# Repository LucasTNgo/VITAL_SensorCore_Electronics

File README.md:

#VITAL Sensor Core Electronics

This ReadMe is empty for now.

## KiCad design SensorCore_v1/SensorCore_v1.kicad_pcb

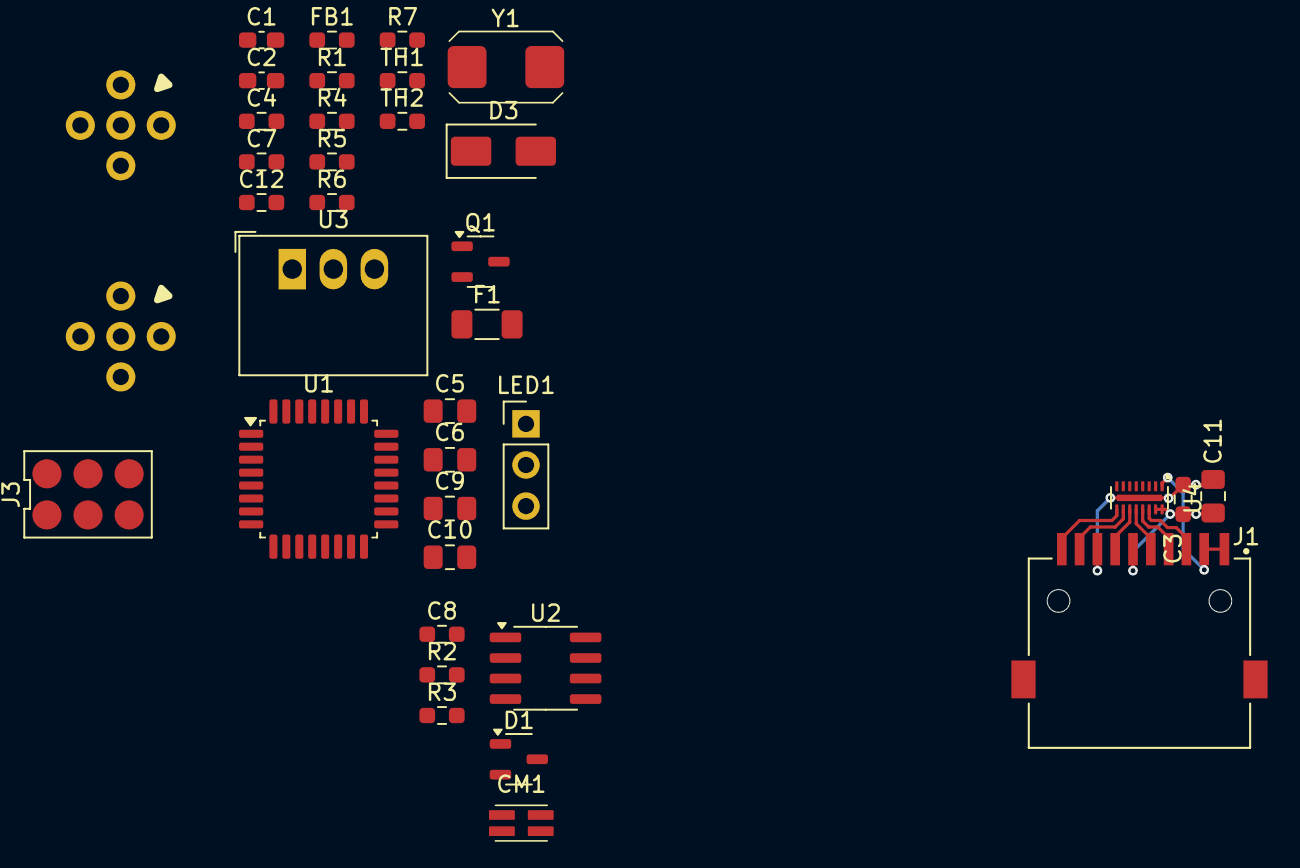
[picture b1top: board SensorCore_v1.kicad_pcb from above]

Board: 4 copper layers, 37 parts (0 on the bottom side), 33 nets.

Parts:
C1, C2: 27pF; C_0603_1608Metric_Pad1.08x0.95mm_HandSolder
C3, C4, C7, C8, C12: 100nF; R_0603_1608Metric_Pad0.98x0.95mm_HandSolder
C5, C6, C9, C10, C11: 10uF 16V; C_0805_2012Metric_Pad1.18x1.45mm_HandSolder
CM1: CM_Choke; CMChoke_2.6x1.2mm_HandSolder
D1: 12V TVS 2CH; SOT-23-3
D3: 12V TVS 1CH; D_SMA
F1: 100mA Polyfuse; R_1206_3216Metric_Pad1.30x1.75mm_HandSolder
FB1: FerriteBead; R_0603_1608Metric_Pad0.98x0.95mm_HandSolder
J1: Micro_SD_Card_Det1; CUI_MSD-11-A
J2, J4: M12x5 A-Type; M12x5_A_Circular_Connector
J3: 2x3 Header; 2x03_2.54mm_DIP_pogo
LED1: RG LED; PinHeader_1x03_P2.54mm_Vertical
Q1: DMN2310U; SOT-23-3
R1, R4: 100k; R_0603_1608Metric_Pad0.98x0.95mm_HandSolder
R2, R3: 10R; R_0603_1608Metric_Pad0.98x0.95mm_HandSolder
R5, R6: 1k; R_0603_1608Metric_Pad0.98x0.95mm_HandSolder
R7: 47k; R_0603_1608Metric_Pad0.98x0.95mm_HandSolder
TH1, TH2: NTC100k B3950 SMT; R_0603_1608Metric_Pad0.98x0.95mm_HandSolder
U1: STM32C092KCT6; LQFP-32_7x7mm_P0.8mm
U2: ATA6563; SOIC-8_3.9x4.9mm_P1.27mm
U3: R-78K3.3-1.0; Converter_DCDC_RECOM_R-78B-2.0_THT
U4: EMIF06-MSD02N16; OnSemi_UDFN-16-1EP_1.35x3.3mm_P0.4mm_EP0.4x2.8mm
Y1: 8MHz 16pF Load; Crystal_6x3.5mm

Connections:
+3V3: C3.2, C4.2, C5.1, C6.1, C7.2, C9.1, C11.1, J1.4 (VDD), J3.5, R7.1, TH1.1, TH2.1, U1.4 (VDD/VDDA), U2.5 (VIO), U3.3 (OUT), U4.15 (VCC), U4.16 (RDATA_VCC)
+5V: C8.1, C10.1, C12.2, FB1.2, LED1.2 (A), U2.3 (VDD), U3.1 (IN)
+5Vin: F1.2, J2.1, J4.1
/CANH: D1.1 (A1), J2.2, J4.2, R2.2
/CANL: D1.2 (A2), J2.4, J4.4, R3.2
/CAN_RXD: U1.29 (PB5), U2.4 (RXD)
/CAN_TXD: U1.30 (PB6), U2.1 (TXD)
/EN_LED_G: R5.1, U1.1 (PB9)
/EN_LED_R: Q1.1 (G), R7.2, U1.32 (PB8)
/NRST: J3.2, U1.6 (PF2-NRST)
/OSC+: C1.1, U1.3 (PC15-OSCX_OUT), Y1.1
/OSC-: C2.1, U1.2 (PC14-OSCX_IN), Y1.2
/SD_Card/Card Detect: J1.9 (DET), U4.1 (WD/CD)
/SWCLK: J3.6, U1.25 (PA14-BOOT0)
/SWDIO: J3.1, U1.24 (PA13)
/TRANSCEIVER_STBY: U1.31 (PB7), U2.8 (STBY)
/VNTC1: R1.1, TH2.2, U1.7 (PA0)
/VNTC2: R4.1, TH1.2, U1.8 (PA1)
GND: C1.2, C2.2, C3.1, C4.1, C5.2, C6.2, C7.1, C8.2, C9.2, C10.2, C11.2, C12.1, D1.3 (common), D3.2 (A2), J1.6 (VSS), J1.10 (SHIELD), J2.3, J3.3, J3.4, J4.3, Q1.2 (S), R1.2, R4.2, U1.5 (VSS/VSSA), U2.2 (VSS), U3.2 (GND), U4.17 (GND)
unnamed: CM1.1, R3.1
unnamed: CM1.3, R2.1
unnamed: D3.1 (A1), F1.1, FB1.1
unnamed: J1.5 (CLK), U4.11 (CLK_EX)
unnamed: J1.3 (CMD), U4.12 (CMD_EX)
unnamed: J1.7 (DAT0), U4.10 (DAT0_EX)
unnamed: J1.8 (DAT1), U4.9 (DAT1_EX)
unnamed: J1.1 (DAT2), U4.14 (DAT2_EX)
unnamed: J1.2 (DAT3/CD), U4.13 (DAT3_EX)
unnamed: LED1.1 (K1), R6.2
unnamed: LED1.3 (K2), R5.2
unnamed: Q1.3 (D), R6.1
unnamed: CM1.4, U2.7 (CANH)
unnamed: CM1.2, U2.6 (CANL)

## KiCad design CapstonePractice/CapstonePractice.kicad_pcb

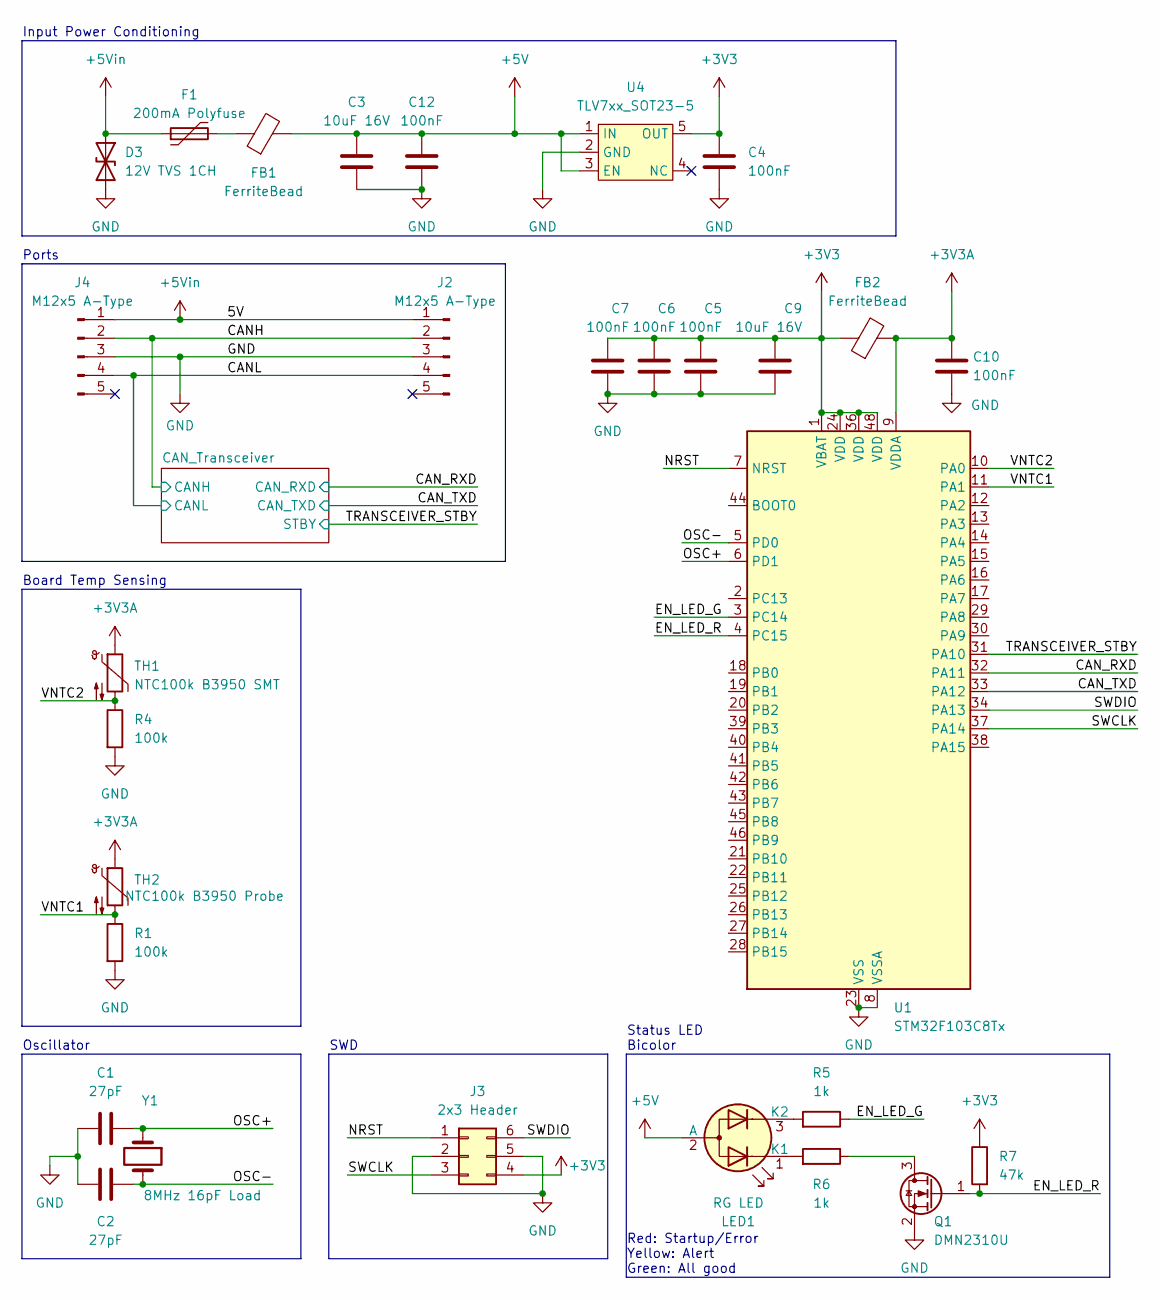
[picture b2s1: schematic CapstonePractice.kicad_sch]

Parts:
C1, C2: 27pF; C_0603_1608Metric_Pad1.08x0.95mm_HandSolder; Digikey Part CL10C270JB8NNNC
C3, C9: 10uF 16V; C_0805_2012Metric_Pad1.18x1.45mm_HandSolder; Digikey Part CL21A106KOQNNNE
C4, C5, C6, C7, C10, C12: 100nF; R_0603_1608Metric_Pad0.98x0.95mm_HandSolder; Digikey Part CL10B104KB8NFNC
D3: 12V TVS 1CH; D_SMA; Digikey Part SMAJ6.0A-13-F
F1: 200mA Polyfuse; R_1206_3216Metric_Pad1.30x1.75mm_HandSolder
FB1, FB2: FerriteBead; R_0603_1608Metric_Pad0.98x0.95mm_HandSolder; Digikey Part MPZ1608S101ATAH0
J2, J4: M12x5 A-Type; M12x5_A_Circular_Connector
J3: 2x3 Header; 2x03_2.54mm_DIP_pogo; Digikey Part 1528-5382-ND
LED1: RG LED; PinHeader_1x03_P2.54mm_Vertical; Digikey Part 5218738F
Q1: DMN2310U; SOT-23-3; Digikey Part DMN2310U
R1, R4: 100k; R_0603_1608Metric_Pad0.98x0.95mm_HandSolder
R5, R6: 1k; R_0603_1608Metric_Pad0.98x0.95mm_HandSolder
R7: 47k; R_0603_1608Metric_Pad0.98x0.95mm_HandSolder
TH1: NTC100k B3950 SMT; R_0603_1608Metric_Pad0.98x0.95mm_HandSolder; Digikey Part JSNB104J395FABXG
TH2: NTC100k B3950 Probe; PinHeader_1x02_P2.54mm_Vertical
U1: STM32F103C8Tx; LQFP-48_7x7mm_P0.5mm; Digikey Part STM32F103C8T6
U4: TLV7xx_SOT23-5; SOT-23-5
Y1: 8MHz 16pF Load; Crystal_6x3.5mm; Digikey Part ABM3-8.000MHZ-D2Y-T

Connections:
+3V3: C4.2, C5.2, C6.2, C7.2, C9.1, FB2.1, J3.4, R7.1, U1.1 (VBAT), U1.24 (VDD), U1.36 (VDD), U1.48 (VDD), U4.5 (OUT); also elsewhere on the board
+3V3A: C10.2, FB2.2, TH1.1, TH2.1, U1.9 (VDDA)
+5V: C3.1, C12.2, FB1.2, LED1.2 (A), U4.1 (IN), U4.3 (EN); also elsewhere on the board
+5Vin: D3.1 (A1), F1.1, J2.1, J4.1
/CANH: J2.2, J4.2; also elsewhere on the board
/CANL: J2.4, J4.4; also elsewhere on the board
/CAN_RXD: U1.32 (PA11); also elsewhere on the board
/CAN_TXD: U1.33 (PA12); also elsewhere on the board
/EN_LED_G: R5.1, U1.3 (PC14)
/EN_LED_R: Q1.1 (G), R7.2, U1.4 (PC15)
/NRST: J3.1, U1.7 (NRST)
/OSC+: C1.1, U1.6 (PD1), Y1.1
/OSC-: C2.1, U1.5 (PD0), Y1.2
/SWCLK: J3.3, U1.37 (PA14)
/SWDIO: J3.6, U1.34 (PA13)
/TRANSCEIVER_STBY: U1.31 (PA10); also elsewhere on the board
/VNTC1: R1.1, TH2.2, U1.11 (PA1)
/VNTC2: R4.1, TH1.2, U1.10 (PA0)
GND: C1.2, C2.2, C3.2, C4.1, C5.1, C6.1, C7.1, C9.2, C10.1, C12.1, D3.2 (A2), J2.3, J3.2, J3.5, J4.3, Q1.2 (S), R1.2, R4.2, U1.8 (VSSA), U1.23 (VSS), U1.35 (VSS), U1.47 (VSS), U4.2 (GND); also elsewhere on the board
unnamed: F1.2, FB1.1
unnamed: LED1.1 (K1), R6.2
unnamed: LED1.3 (K2), R5.2
unnamed: Q1.3 (D), R6.1

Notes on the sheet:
Board Temp Sensing
Oscillator
SWD
Red: Startup/Error Yellow: Alert Green: All good
Ports
Input Power Conditioning
Status LED Bicolor

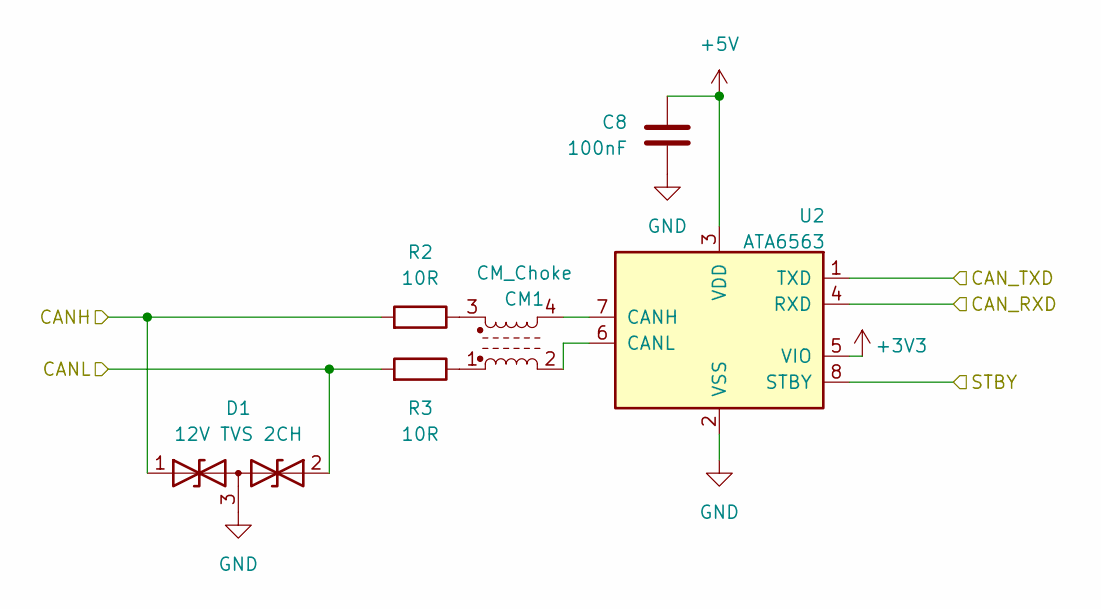
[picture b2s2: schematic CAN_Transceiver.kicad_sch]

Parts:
C8: 100nF; R_0603_1608Metric_Pad0.98x0.95mm_HandSolder; Digikey Part CL10B104KB8NFNC
CM1: CM_Choke; CMChoke_2.6x1.2mm_HandSolder; Digikey Part SCM2012FS181MDG
D1: 12V TVS 2CH; SOT-23-3; Digikey Part DESD12VL2BTQ-7
R2, R3: 10R; R_0603_1608Metric_Pad0.98x0.95mm_HandSolder
U2: ATA6563; SOIC-8_3.9x4.9mm_P1.27mm; Digikey Part ATA6563-GAQW1

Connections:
+3V3: U2.5 (VIO); also elsewhere on the board
+5V: C8.1, U2.3 (VDD); also elsewhere on the board
/CANH: D1.1 (A1), R2.2; also elsewhere on the board
/CANL: D1.2 (A2), R3.2; also elsewhere on the board
/CAN_RXD: U2.4 (RXD); also elsewhere on the board
/CAN_TXD: U2.1 (TXD); also elsewhere on the board
/TRANSCEIVER_STBY: U2.8 (STBY); also elsewhere on the board
GND: C8.2, D1.3 (common), U2.2 (VSS); also elsewhere on the board
unnamed: CM1.1, R3.1
unnamed: CM1.3, R2.1
unnamed: CM1.4, U2.7 (CANH)
unnamed: CM1.2, U2.6 (CANL)

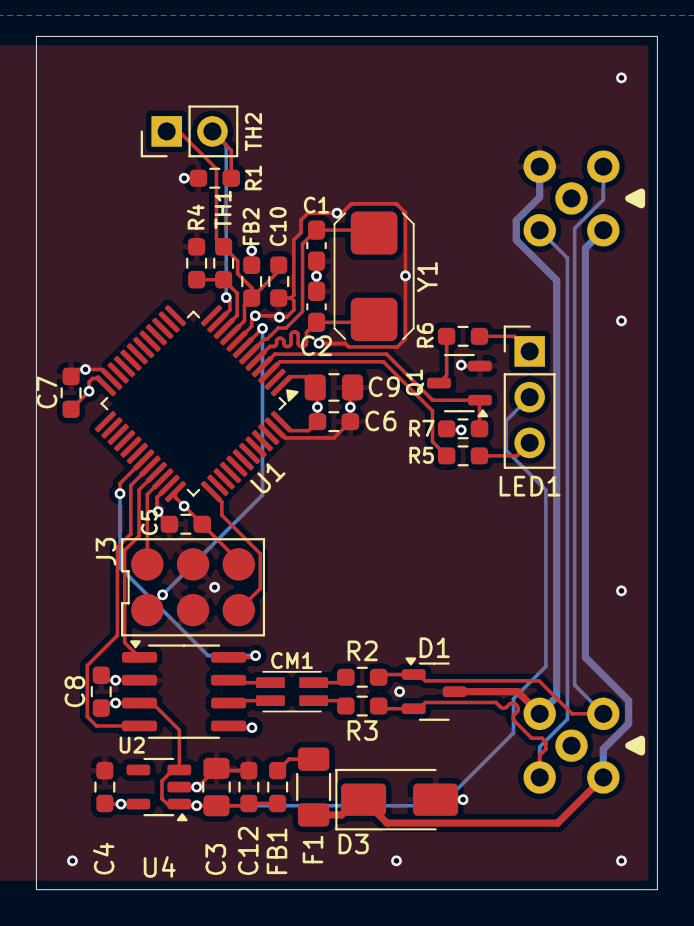
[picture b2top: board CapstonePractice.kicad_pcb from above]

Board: 4 copper layers, 34.5 x 47.4 mm, 35 parts (0 on the bottom side), 27 nets.

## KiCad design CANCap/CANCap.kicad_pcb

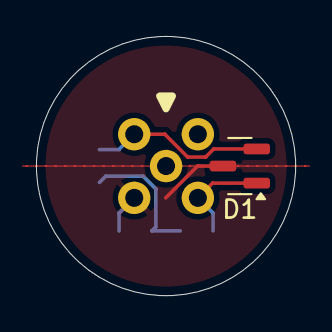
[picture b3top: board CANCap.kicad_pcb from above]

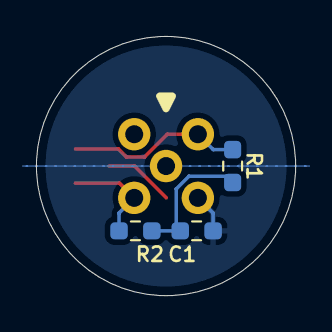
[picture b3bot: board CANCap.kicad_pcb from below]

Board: 2 copper layers, 14.4 x 14.4 mm, 5 parts (3 on the bottom side), 4 nets.

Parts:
C1: 100nF; R_0603_1608Metric_Pad0.98x0.95mm_HandSolder
D1: 7V TVS; SOT-23
J1: M12x5 A-Type; M12x5_A_Circular_Connector
R1, R2: 60; R_0603_1608Metric_Pad0.98x0.95mm_HandSolder

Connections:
/CANH: D1.2 (A2), J1.2, R1.1
/CANL: D1.1 (A1), J1.4, R2.2
GND: C1.2, D1.3 (common), J1.3
unnamed: C1.1, R1.2, R2.1

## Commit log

2026-03-22 Added CANCap
2026-03-22 Added CapstonePractice
2026-03-22 Added SensorCore and SensorPack
2026-04-05 Misc. Tweaks to files
